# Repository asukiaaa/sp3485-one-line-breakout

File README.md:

# sp3485-one-line-breakout

## Setup

To install submodules, run the following command after clone.

```
git submodule update --init --recursive
```

## License

MIT

## References

- [Sparkfun RS485 Transceiver Breakout](https://www.sparkfun.com/products/10124)
- [Sparkfun RS485 Transceiver Breakout schematic (PDF)](https://cdn.sparkfun.com/datasheets/BreakoutBoards/RS485_Breakout_v10.pdf)

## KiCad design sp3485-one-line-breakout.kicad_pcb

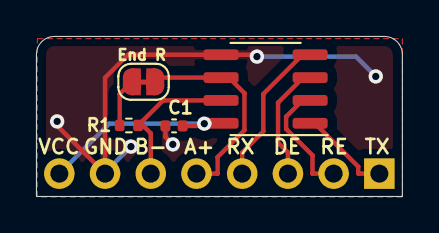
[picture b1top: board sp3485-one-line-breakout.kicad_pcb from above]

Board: 2 copper layers, 20.3 x 8.9 mm, 5 parts (0 on the bottom side), 9 nets.

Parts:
C1: 0.1uf; C_0402_1005Metric
J1: Conn_01x08; PinHeader_1x08_P2.54mm_Vertical_witout_silk
JP1: Bridged; SolderJumper-2_P1.3mm_Bridged_RoundedPad1.0x1.5mm
R1: 220; R_0402_1005Metric
U1: SP3485CN; SOIC-8_3.9x4.9mm_P1.27mm

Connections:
/A: J1.5, JP1.1, U1.6
/B: J1.6, R1.2, U1.7
/DE: J1.3, U1.3
/DI: J1.4, U1.4
/RE: J1.2, U1.2
/RO: J1.1, U1.1
GND: C1.2, J1.7, U1.5
unnamed: JP1.2, R1.1
VCC: C1.1, J1.8, U1.8

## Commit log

2020-11-15 Add command to setup submodule on readme
2020-11-15 Plot schematic
2020-12-15 Add image to readme
2021-04-29 Change resistor size and add capacitor
2023-04-16 Add bom
2023-04-16 Add shop link to readme
